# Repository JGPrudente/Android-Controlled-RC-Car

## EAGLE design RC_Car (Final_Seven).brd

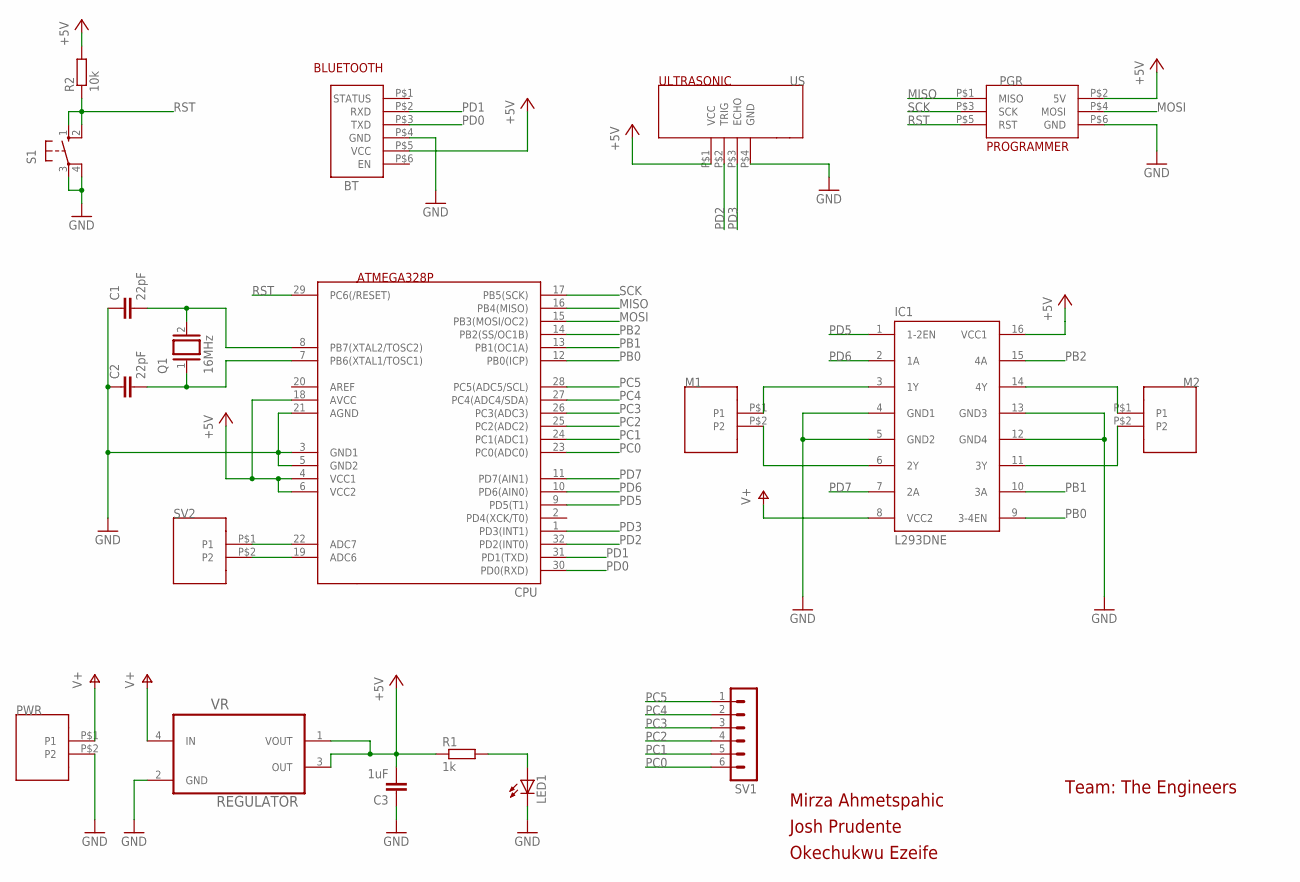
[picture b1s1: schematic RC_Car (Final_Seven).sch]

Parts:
BT: BLUETOOTH
C1, C2: 22pF; C025-030X050
C3: 1uF; C025-030X050
CPU: ATMEGA328P
IC1: L293DNE
LED1: LED3MM; HLMP-D105
M1, M2: HEADER
PGR: AVR6AVR6; AVR6
PWR: HEADER
Q1: 16MHz; QS
R1: 1k; 0207/10
R2: 10k; 0207/10
S1: 10-XX; B3F-10XX
SV1: MA06-1
SV2: HEADER
US: ULTRASONIC
VR: REGULATOR

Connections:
+5V: BT.P$5 (VCC), C3.2, CPU.4 (VCC1), CPU.6 (VCC2), CPU.18 (AVCC), IC1.16 (VCC1), PGR.P$2 (5V), R1.1, R2.2, US.P$1 (VCC), VR.1 (VOUT), VR.3 (OUT)
GND: BT.P$4 (GND), C1.1, C2.1, C3.1, CPU.3 (GND1), CPU.5 (GND2), CPU.21 (AGND), IC1.4 (GND1), IC1.5 (GND2), IC1.12 (GND4), IC1.13 (GND3), LED1.K (C), PGR.P$6 (GND), PWR.P$2 (P2), S1.3, S1.4 (P1), US.P$4 (GND), VR.2 (GND)
MISO: CPU.16 (PB4(MISO)), PGR.P$1 (MISO)
MOSI: CPU.15 (PB3(MOSI/OC2)), PGR.P$4 (MOSI)
unnamed: IC1.6 (2Y), M1.P$2 (P2)
unnamed: C2.2, CPU.7 (PB6(XTAL1/TOSC1)), Q1.1
unnamed: C1.2, CPU.8 (PB7(XTAL2/TOSC2)), Q1.2
unnamed: LED1.A, R1.2
unnamed: CPU.22 (ADC7), SV2.P$1 (P1)
unnamed: IC1.14 (4Y), M2.P$1 (P1)
unnamed: IC1.11 (3Y), M2.P$2 (P2)
unnamed: IC1.3 (1Y), M1.P$1 (P1)
unnamed: CPU.19 (ADC6), SV2.P$2 (P2)
PB0: CPU.12 (PB0(ICP)), IC1.9 (3-4EN)
PB1: CPU.13 (PB1(OC1A)), IC1.10 (3A)
PB2: CPU.14 (PB2(SS/OC1B)), IC1.15 (4A)
PC0: CPU.23 (PC0(ADC0)), SV1.6
PC1: CPU.24 (PC1(ADC1)), SV1.5
PC2: CPU.25 (PC2(ADC2)), SV1.4
PC3: CPU.26 (PC3(ADC3)), SV1.3
PC4: CPU.27 (PC4(ADC4/SDA)), SV1.2
PC5: CPU.28 (PC5(ADC5/SCL)), SV1.1
PD0: BT.P$3 (TXD), CPU.30 (PD0(RXD))
PD1: BT.P$2 (RXD), CPU.31 (PD1(TXD))
PD2: CPU.32 (PD2(INT0)), US.P$2 (TRIG)
PD3: CPU.1 (PD3(INT1)), US.P$3 (ECHO)
PD5: CPU.9 (PD5(T1)), IC1.1 (1-2EN)
PD6: CPU.10 (PD6(AIN0)), IC1.2 (1A)
PD7: CPU.11 (PD7(AIN1)), IC1.7 (2A)
RST: CPU.29 (PC6(/RESET)), PGR.P$5 (RST), R2.1, S1.1 (S), S1.2 (S1)
SCK: CPU.17 (PB5(SCK)), PGR.P$3 (SCK)
V+: IC1.8 (VCC2), PWR.P$1 (P1), VR.4 (IN)

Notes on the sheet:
Josh Prudente
Mirza Ahmetspahic
Okechukwu Ezeife
Team: The Engineers
CPU
PGR
PWR
SV2

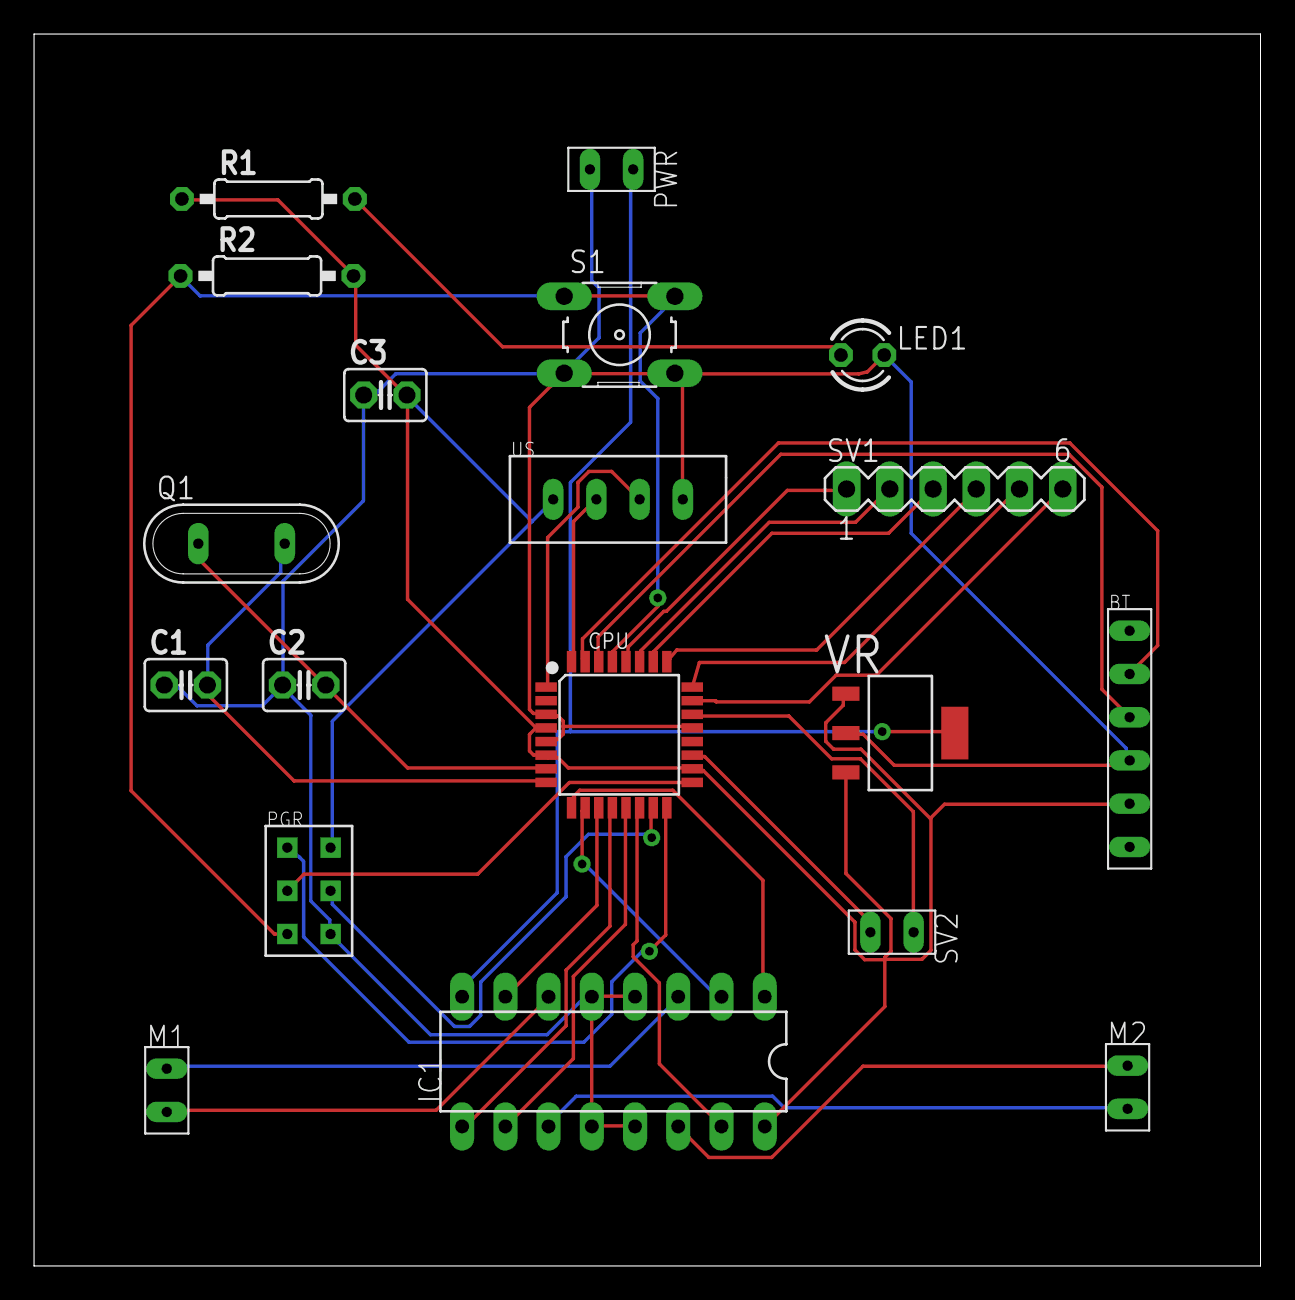
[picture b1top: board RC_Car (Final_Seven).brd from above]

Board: 2 copper layers, 72.1 x 72.4 mm, 19 parts (0 on the bottom side), 32 nets.

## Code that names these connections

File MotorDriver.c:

#define F_CPU 16000000UL

#include <avr/io.h>
#include <util/delay.h>

int main(void)
{
    DDRD = 0b11000000;    //PD6 and PD7 in PORTD are outputs
    DDRB = 0b00000110;	//PB1 and Pb2 in PORTB are outputs

    while (1) 
	{
		/* Uncomment lines to manipulate which wheels to move */
		//PORTD = 0b01000000;   //PD6 is high	moves left wheel backwards
		//PORTB = 0b00000100;	//PB2 is high	moves right wheel forward
		//PORTD = 0b10000000;	//PD7 is high	moves left wheel forward
		//PORTB = 0b00000010;	//PB1 is high	moves right wheel backwards
		
		// Wheels stop
		//PORTD = 0b10000000;	
		//PORTB = 0b00000010;
    }
}
